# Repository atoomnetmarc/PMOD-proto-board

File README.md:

# PMOD proto board

My [Kicad library](https://github.com/atoomnetmarc/ATOOMNETKICAD) is used in this project.

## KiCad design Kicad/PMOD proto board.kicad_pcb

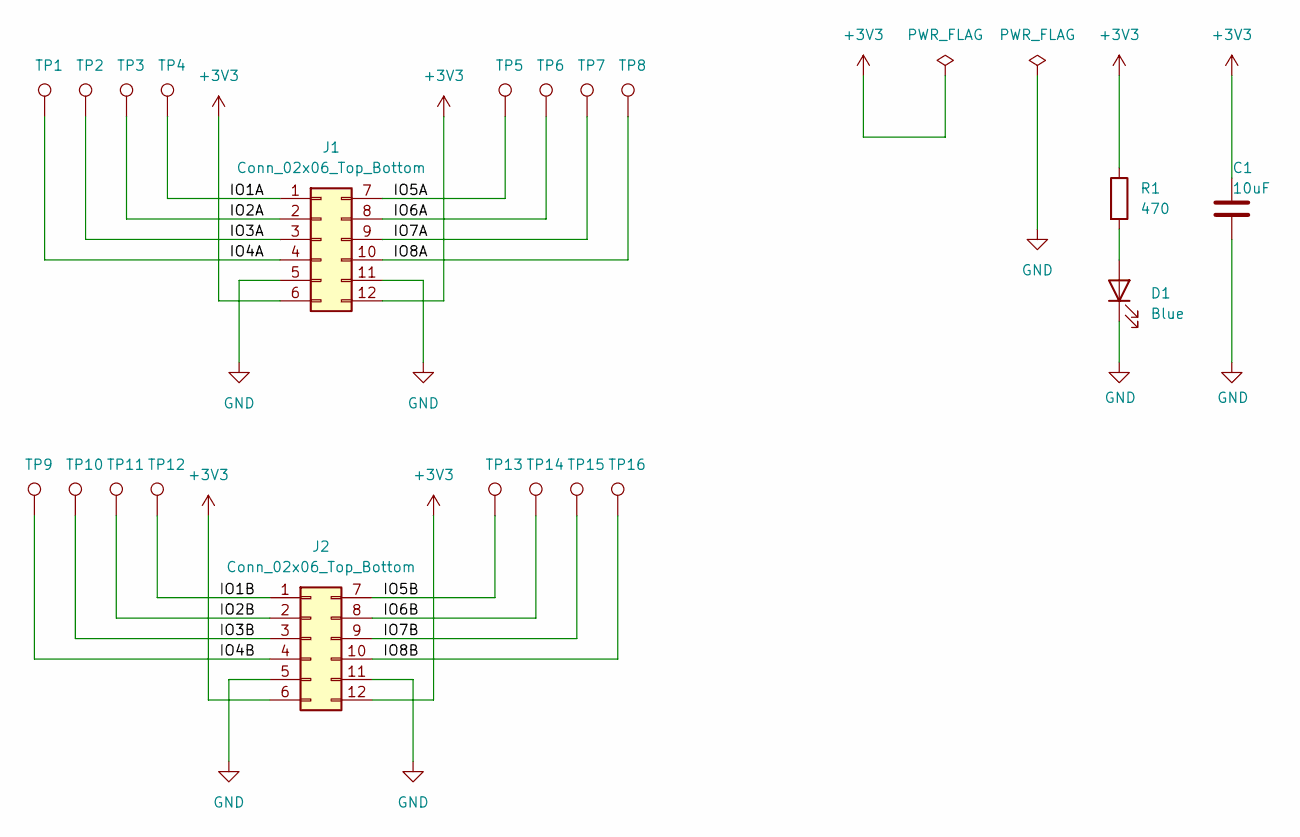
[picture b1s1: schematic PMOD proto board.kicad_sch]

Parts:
C1: 10uF; C_0805_2012Metric_Pad1.18x1.45mm_HandSolder
D1: Blue; LED_0805_2012Metric_Pad1.15x1.40mm_HandSolder
J1, J2: Conn_02x06_Top_Bottom; PinHeader_2x06_P2.54mm_Horizontal_Top_Bottom
R1: 470; R_0805_2012Metric_Pad1.20x1.40mm_HandSolder
TP1, TP2, TP3, TP4, TP5, TP6, TP7, TP8, TP9, TP10, TP11, TP12, TP13, TP14, TP15, TP16: TestPoint; TestPoint_THTPad_D1.7mm_Drill1.0mm-naked

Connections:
+3V3: C1.1, J1.6, J1.12, J2.6, J2.12, R1.1
/IO1A: J1.1, TP4.1
/IO1B: J2.1, TP12.1
/IO2A: J1.2, TP3.1
/IO2B: J2.2, TP11.1
/IO3A: J1.3, TP2.1
/IO3B: J2.3, TP10.1
/IO4A: J1.4, TP1.1
/IO4B: J2.4, TP9.1
/IO5A: J1.7, TP5.1
/IO5B: J2.7, TP13.1
/IO6A: J1.8, TP6.1
/IO6B: J2.8, TP14.1
/IO7A: J1.9, TP7.1
/IO7B: J2.9, TP15.1
/IO8A: J1.10, TP8.1
/IO8B: J2.10, TP16.1
GND: C1.2, D1.1 (K), J1.5, J1.11, J2.5, J2.11
unnamed: D1.2 (A), R1.2

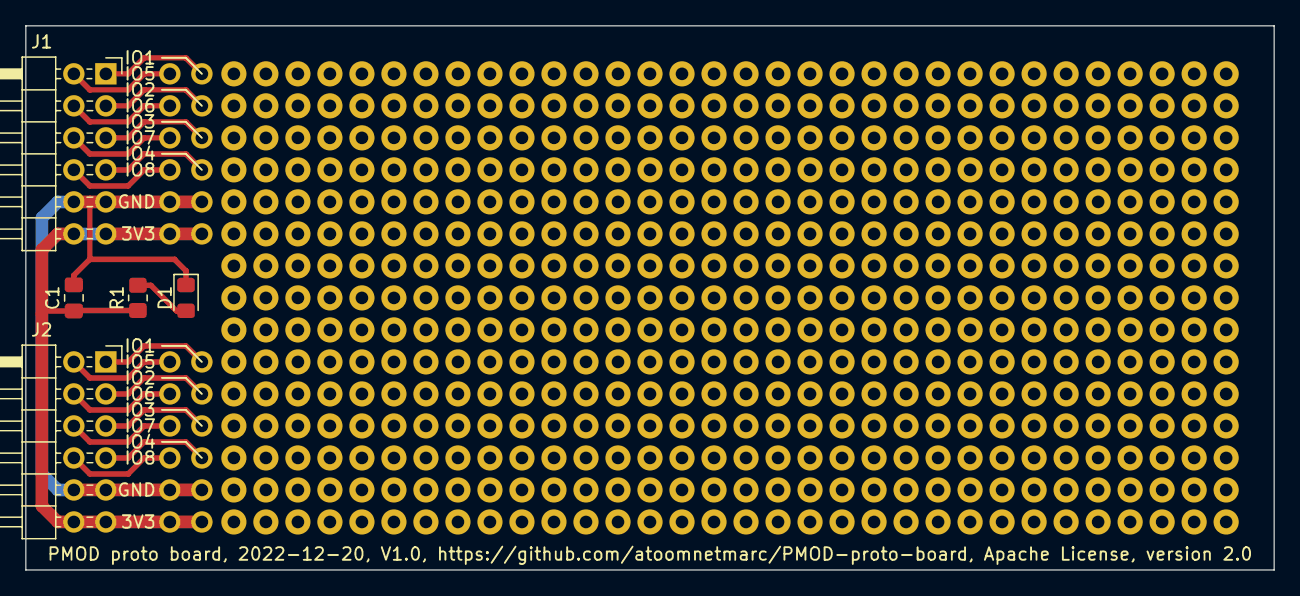
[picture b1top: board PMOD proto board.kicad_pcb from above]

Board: 2 copper layers, 99.1 x 43.2 mm, 21 parts (0 on the bottom side), 19 nets.

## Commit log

2022-11-21 Initial commit.
2022-12-06 Add photo of real board.
2022-12-06 Add link to ATOOMNETKICAD

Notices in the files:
Kicad/PMOD proto board.kicad_pcb:
PMOD proto board, 2022-12-20, V1.0, https://github.com/atoomnetmarc/PMOD-proto-board, Apache License, version 2.0
README.md:
License: Apache 2.0
